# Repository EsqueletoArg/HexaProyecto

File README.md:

# HexaProyecto

Es  ajedrez de 3x3 casillas, donde se enfrentan 3 peones de ambos bandos para inmovilizar al rival o llegar al otro lado del tablero.

# Software:
* Programado para ser subido en un ESP32, este proyecto cuenta con un algoritmo que actua como el rival de este ajedrez. Este software se encuentra en la carpeta **/Firmware**, en el archivo nombrado "*HexaProyecto.ino*" y fue programado a mano usando Arduino IDE. Si desean construir uno en sus hogares, en las primeras lineas de esta programacion deberían cambiar ciertos valores para que el proyecto pueda conectarse a internet correctamente.

* En cuanto al servidor, se encuentra alojado en la carpeta **/Firmware/Server** en el archivo "*Servidor.js*". Para hacerlo funcionar, necesitamos descargar los programas Node.js y Mosquitto, ambos son descargables de manera gratuita en su respectiva página oficial. 

* Para hacerlo funcionar correctamente, hay que descargar ciertas dependencias en la carpeta donde se encuentre el servidor. Estas dependencias no funcionaran sin Nodejs y/o Mosquitto. Para descargarlas hay que dirigirse al directorio donde se encuentra el archivo "*Servidor.js*" via cmd e introducir los comandos "*npm init -y*" y "*npm install mqtt express body-parser*". Descargar cada dependencia podría tardar un tiempo, pero no de manera significativa.

# Hardware (PCB):
* El hardware de la PCB se encuentra en la carpeta **/Hardware_(PCB)**. Cada archivo dentro de esta carpeta es parte del diseño del PCB, desde el PCB final, hasta el esquema usado como referencia.

* Como el ESP32 está conectado al internet, esto reducía enormemente la cantidad de pines (Entradas y salidas), que podiamos usar. Por eso decidimos hacer una matriz de botones, lo que nos permitio reducir la cantidad de pines usados de 9 a 6.

* Para la placa usamos unos LEDs inteligentes llamados "WS2812", que con cierto nivel de programación son capaces de formar cualquier color. Estos LEDs solo necesitan una fuente de alimentacion de 5V, GND y una entrada de datos. Estos LEDs tambien tienen un cable de salida de datos que nos permitió poner 9 LEDs en serie y, por tanto, usar una sola salida del ESP32.

# Hardware (3D):
* Para el 3D hicimos un marco para encajar la PCB. Si bien puede sonar a que es por motivos de poco esfuerzo, la verdad es otra: Es algo simple, barato y que le permite al PCB relucir todo el esfuerzo que le dedicamos para diseñarlo.

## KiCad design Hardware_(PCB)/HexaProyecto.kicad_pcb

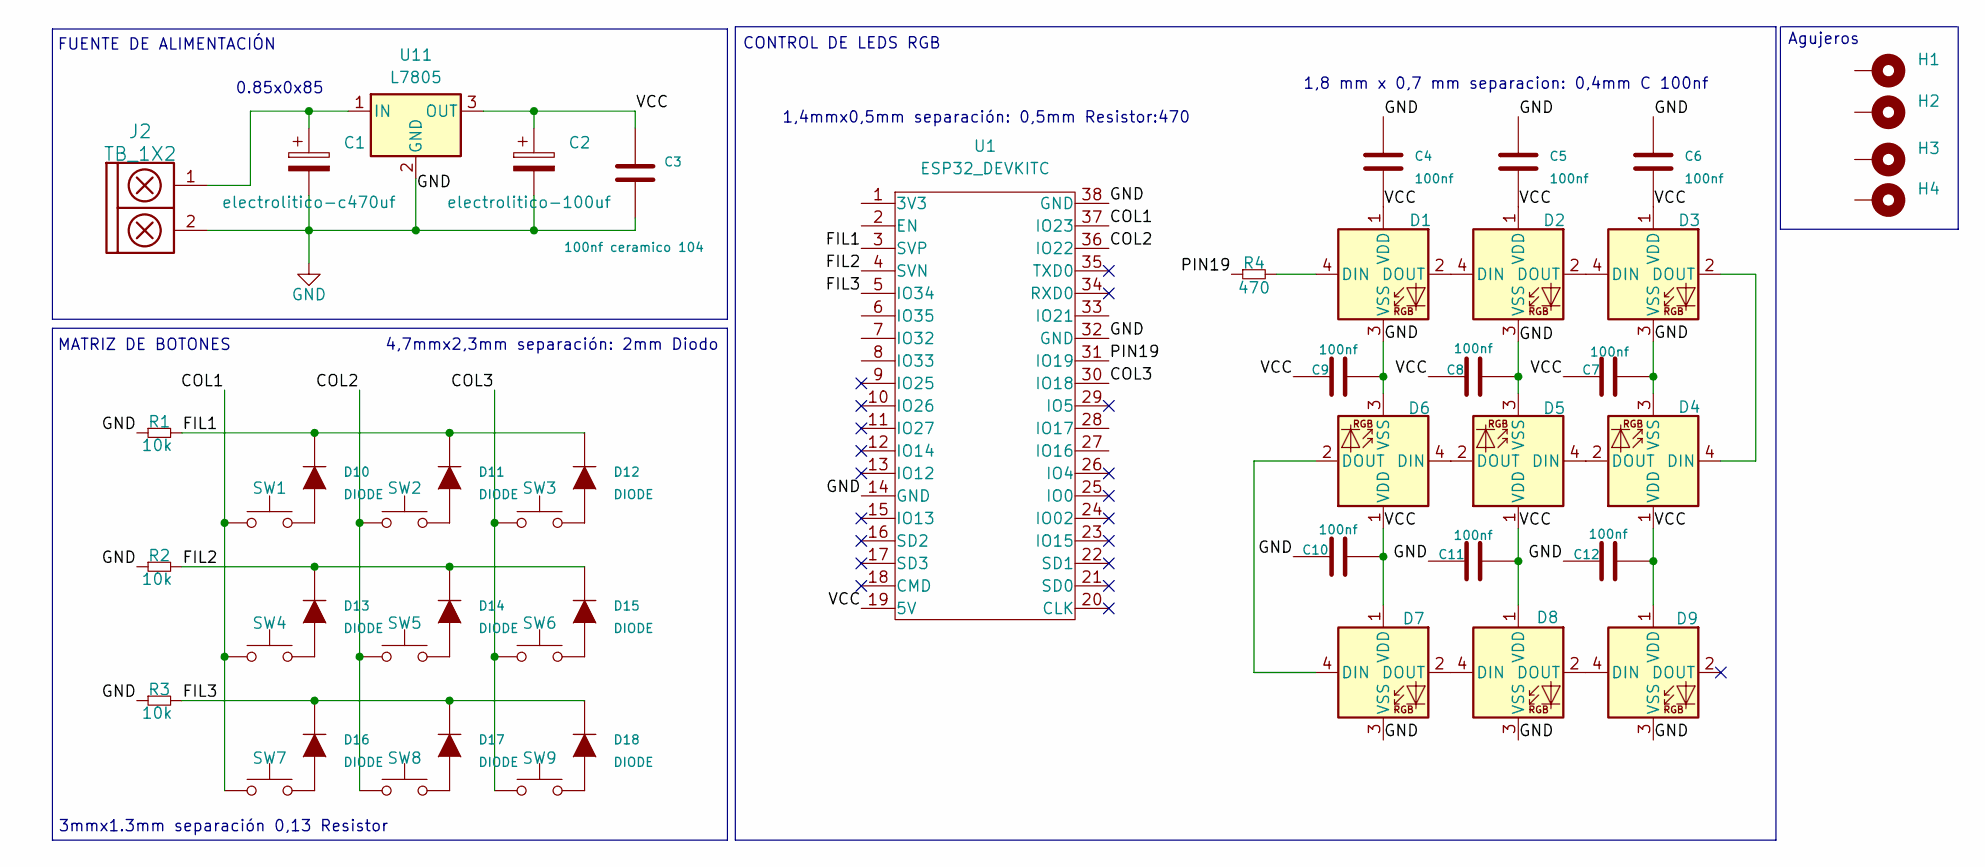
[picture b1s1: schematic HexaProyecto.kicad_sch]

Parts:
C1: electrolitico-c470uf; CP_Elec_6.3x9.9
C2: electrolitico-100uf; CP_Radial_D8.0mm_P3.50mm
C3: 100nf ceramico 104; CAP_0.1
C4, C5, C6, C7, C8, C9, C10, C11, C12: 100nf; verdadero.capacior.smd.100nf
D1, D2, D3, D4, D5, D6, D7, D8, D9: WS2812B; LED_WS2812B_PLCC4_5.0x5.0mm_P3.2mm
D10, D11, D12, D13, D14, D15, D16, D17, D18: DIODE; Diodo_SMD M7
H1, H2, H3, H4: MountingHole_Pad; Separador_M3_10mm
J2: TB_1X2; TerminalBlock_Altech_AK300-2_P5.00mm
R1, R2, R3: 10k; rrr
R4: 470; R_0603_1608Metric
SW1, SW2, SW3, SW4, SW5, SW6, SW7, SW8, SW9: SW_Push; pushbuttom
U1: ESP32_DEVKITC; ese
U11: L7805; TO-263-2

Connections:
/COL1: SW1.1, SW4.1, SW7.1, U1.37 (IO23)
/COL2: SW2.1, SW5.1, SW8.1, U1.36 (IO22)
/COL3: SW3.1, SW6.1, SW9.1, U1.30 (IO18)
/FIL1: D10.2 (K), D11.2 (K), D12.2 (K), R1.2, U1.3 (SVP)
/FIL2: D13.2 (K), D14.2 (K), D15.2 (K), R2.2, U1.4 (SVN)
/FIL3: D16.2 (K), D17.2 (K), D18.2 (K), R3.2, U1.5 (IO34)
/PIN19: R4.1, U1.31 (IO19)
/VCC: C2.1, C3.2, C4.1, C5.1, C6.1, C7.1, C8.1, C9.1, C10.1, C11.1, C12.1, D1.1 (VDD), D2.1 (VDD), D3.1 (VDD), D4.1 (VDD), D5.1 (VDD), D6.1 (VDD), D7.1 (VDD), D8.1 (VDD), D9.1 (VDD), U1.19 (5V), U11.3 (OUT)
GND: C1.2, C2.2, C3.1, C4.2, C5.2, C6.2, C7.2, C8.2, C9.2, C10.2, C11.2, C12.2, D1.3 (VSS), D2.3 (VSS), D3.3 (VSS), D4.3 (VSS), D5.3 (VSS), D6.3 (VSS), D7.3 (VSS), D8.3 (VSS), D9.3 (VSS), J2.2, R1.1, R2.1, R3.1, U1.14 (GND), U1.32 (GND), U1.38 (GND), U11.2 (GND)
unnamed: D1.4 (DIN), R4.2
unnamed: D1.2 (DOUT), D2.4 (DIN)
unnamed: D2.2 (DOUT), D3.4 (DIN)
unnamed: D3.2 (DOUT), D4.4 (DIN)
unnamed: D4.2 (DOUT), D5.4 (DIN)
unnamed: D5.2 (DOUT), D6.4 (DIN)
unnamed: D6.2 (DOUT), D7.4 (DIN)
unnamed: D7.2 (DOUT), D8.4 (DIN)
unnamed: D8.2 (DOUT), D9.4 (DIN)
unnamed: D10.1 (A), SW1.2
unnamed: D11.1 (A), SW2.2
unnamed: D12.1 (A), SW3.2
unnamed: D13.1 (A), SW4.2
unnamed: D14.1 (A), SW5.2
unnamed: D15.1 (A), SW6.2
unnamed: D16.1 (A), SW7.2
unnamed: D17.1 (A), SW8.2
unnamed: D18.1 (A), SW9.2
unnamed: C1.1, J2.1, U11.1 (IN)

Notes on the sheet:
FUENTE DE ALIMENTACIÓN
0.85x0x85
3mmx1.3mm separación 0,13 Resistor
1,8 mm x 0,7 mm separacion: 0,4mm C 100nf
MATRIZ DE BOTONES
Agujeros
CONTROL DE LEDS RGB
4,7mmx2,3mm separación: 2mm Diodo
1,4mmx0,5mm separación: 0,5mm Resistor:470

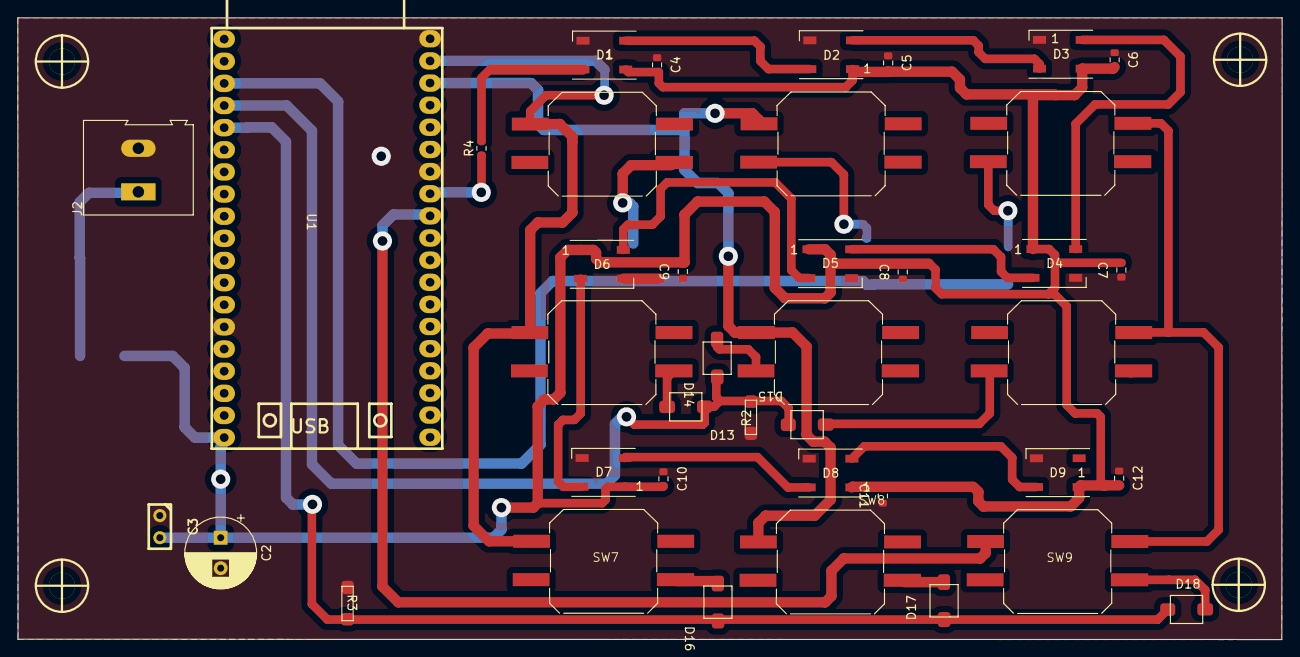
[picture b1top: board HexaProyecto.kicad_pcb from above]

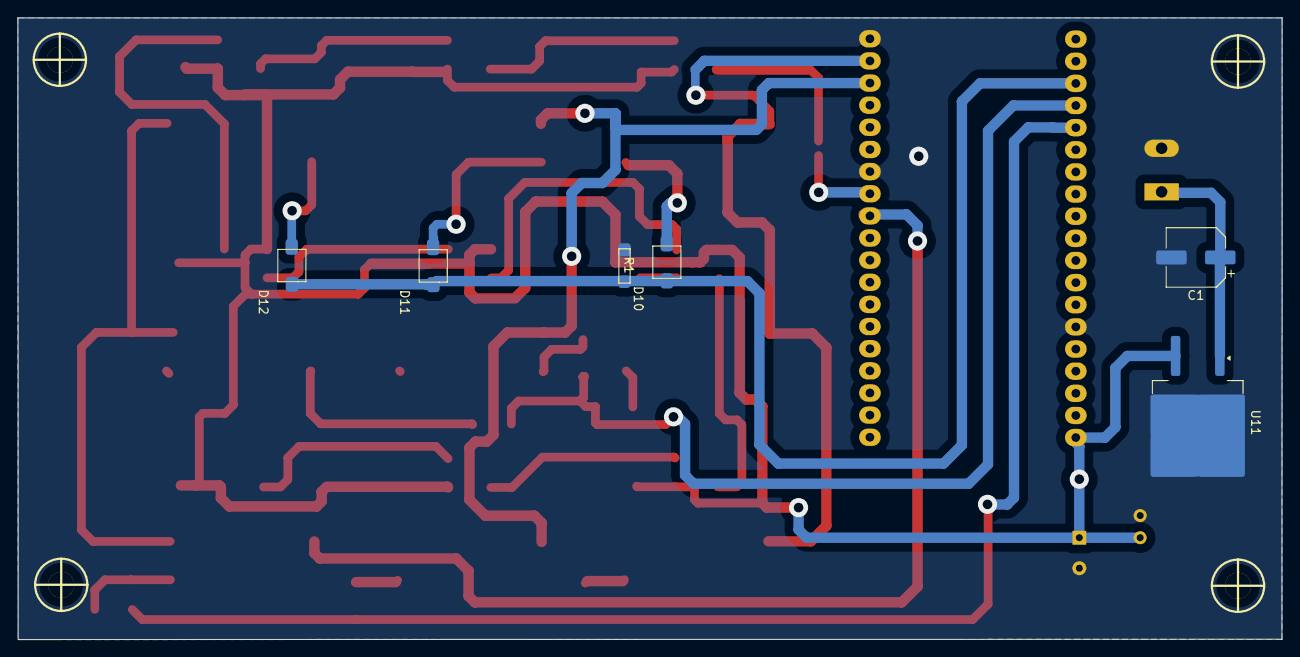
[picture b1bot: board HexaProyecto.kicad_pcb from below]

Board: 2 copper layers, 145.1 x 71.3 mm, 50 parts (6 on the bottom side), 28 nets.

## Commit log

2024-11-20 Proyectolol
2024-11-20 Servidor nodejs
2024-11-21 Kicads
2024-11-27 Create Hardware_PCB
2024-11-28 Rename HexaProyecto.ino to Software/HexaProyecto.ino
2024-11-28 Rename lll.kicad_pro to Hardware_(PCB)/HexaProyecto.kicad_pro
2024-11-28 Rename HexaProyecto_3D.stl to Hardware_(3D)/HexaProyecto_3D.stl
